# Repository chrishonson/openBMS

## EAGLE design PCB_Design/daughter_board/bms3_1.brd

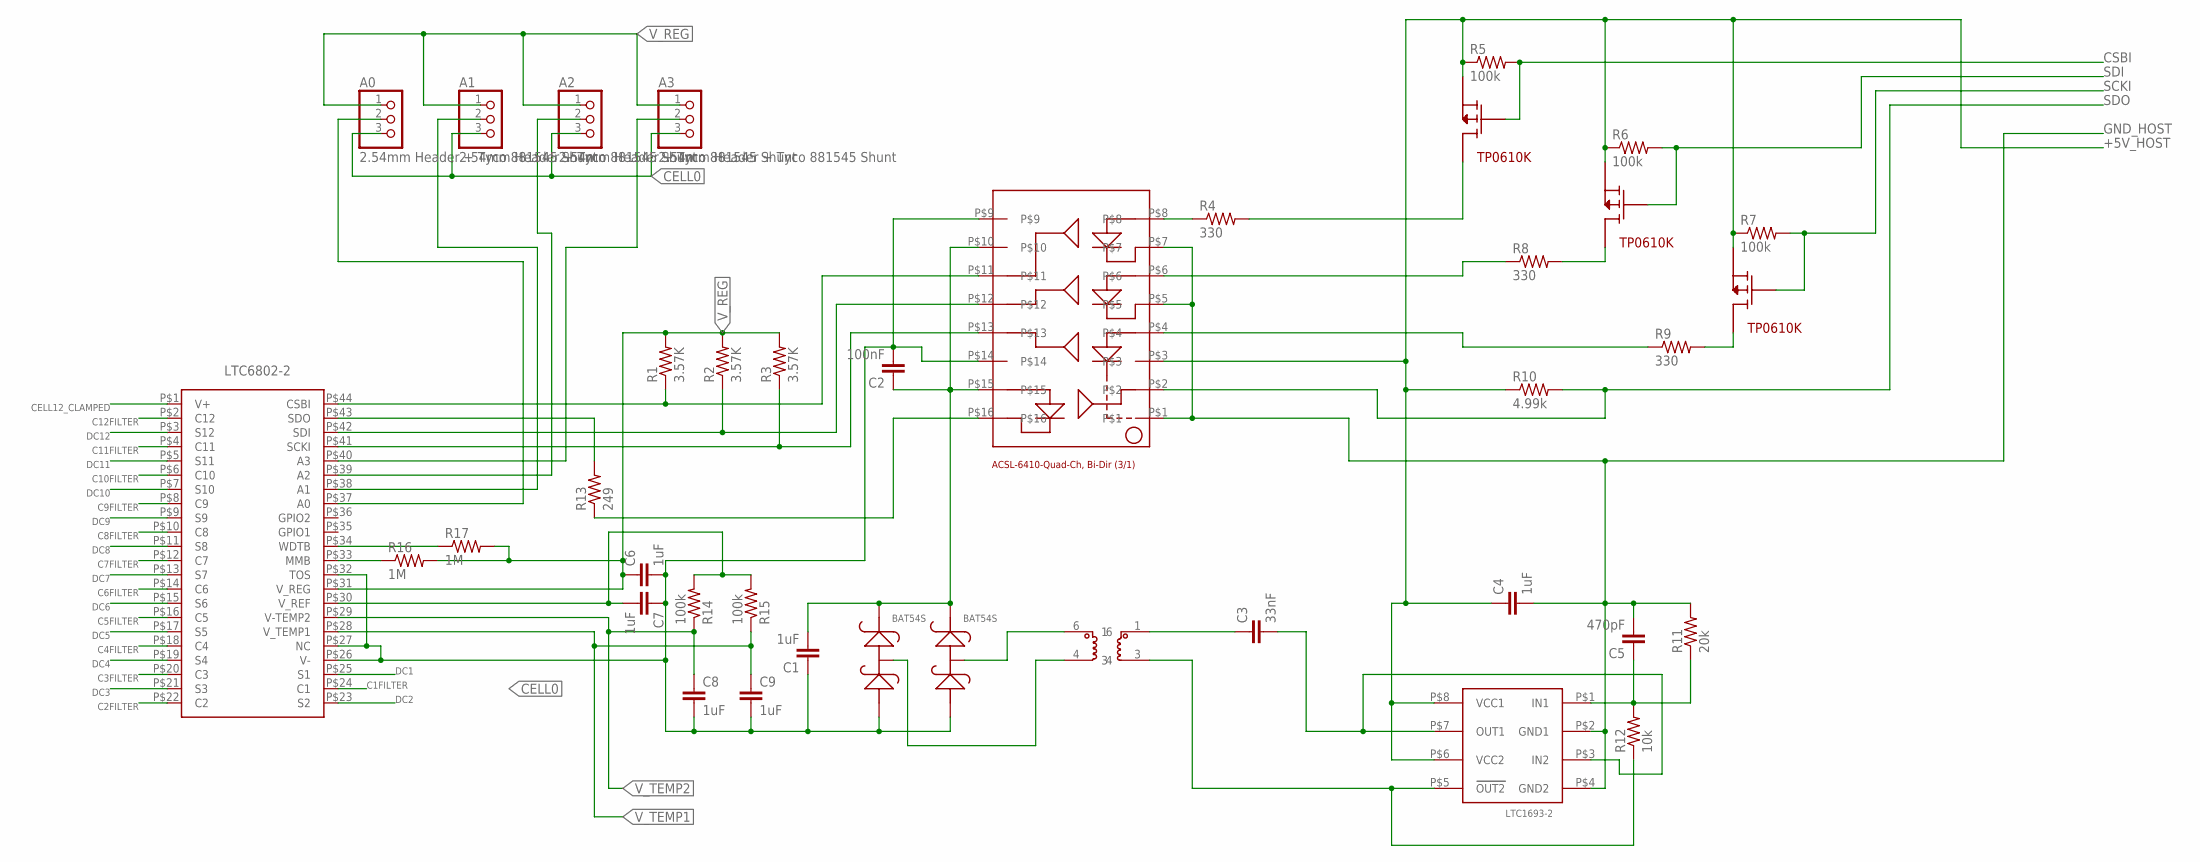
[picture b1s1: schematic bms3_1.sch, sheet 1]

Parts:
A0, A1, A2, A3: 2.54mm Header + Tyco 881545 Shunt; 1X03
ACSL6410: ACSL-6410; ACSL-6410-SO16
BAT1, BAT2: BAT54S; SOT-23
C1, C4, C6, C7, C8, C9: 1uF; C0603
C2: 100nF; C0603
C3: 33nF; C0603
C5: 470pF; C0603
CSBI: TP0610K; SOT-23
LTC1693: LTC1693-2; S8-LTC1693-2
PE68386: PE68386
R1, R2, R3: 3.57K; R0603
R4, R8, R9: 330; R0603
R5, R6, R7, R14, R15: 100k; R0603
R10: 4.99k; R0603
R11: 20k; R0603
R12: 10k; R0603
R13: 249; R0603
R16, R17: 1M; R0603
SCKI: TP0610K; SOT-23
SDI: TP0610K; SOT-23
X-BMS: LTC6802-2; SSOP-44

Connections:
+5V_HOST: ACSL6410.P$3, C4.1, CSBI.2, LTC1693.P$6 (VCC2), LTC1693.P$8 (VCC1), R5.1, R6.1, R7.1, R10.1, SCKI.2, SDI.2; also elsewhere on the board
C1FILTER: X-BMS.P$24 (C1); also elsewhere on the board
C2FILTER: X-BMS.P$22 (C2); also elsewhere on the board
C3FILTER: X-BMS.P$20 (C3); also elsewhere on the board
C4FILTER: X-BMS.P$18 (C4); also elsewhere on the board
C5FILTER: X-BMS.P$16 (C5); also elsewhere on the board
C6FILTER: X-BMS.P$14 (C6); also elsewhere on the board
C7FILTER: X-BMS.P$12 (C7); also elsewhere on the board
C8FILTER: X-BMS.P$10 (C8); also elsewhere on the board
C9FILTER: X-BMS.P$8 (C9); also elsewhere on the board
C10FILTER: X-BMS.P$6 (C10); also elsewhere on the board
C11FILTER: X-BMS.P$4 (C11); also elsewhere on the board
C12FILTER: X-BMS.P$2 (C12); also elsewhere on the board
CELL0: A0.3, A1.3, A2.3, A3.3, ACSL6410.P$9, ACSL6410.P$14, BAT1.1, BAT2.1, C1.1, C2.2, C6.2, C7.1, C8.2, C9.2, X-BMS.P$26 (V-), X-BMS.P$27 (NC), X-BMS.P$32 (TOS); also elsewhere on the board
CELL12_CLAMPED: X-BMS.P$1 (V+); also elsewhere on the board
CSBI: CSBI.1, R5.2; also elsewhere on the board
DC1: X-BMS.P$25 (S1); also elsewhere on the board
DC2: X-BMS.P$23 (S2); also elsewhere on the board
DC3: X-BMS.P$21 (S3); also elsewhere on the board
DC4: X-BMS.P$19 (S4); also elsewhere on the board
DC5: X-BMS.P$17 (S5); also elsewhere on the board
DC6: X-BMS.P$15 (S6); also elsewhere on the board
DC7: X-BMS.P$13 (S7); also elsewhere on the board
DC8: X-BMS.P$11 (S8); also elsewhere on the board
DC9: X-BMS.P$9 (S9); also elsewhere on the board
DC10: X-BMS.P$7 (S10); also elsewhere on the board
DC11: X-BMS.P$5 (S11); also elsewhere on the board
DC12: X-BMS.P$3 (S12); also elsewhere on the board
GND_HOST: ACSL6410.P$1, ACSL6410.P$5, ACSL6410.P$7, C4.2, C5.2, LTC1693.P$2 (GND1), LTC1693.P$4 (GND2), R11.2; also elsewhere on the board
unnamed: ACSL6410.P$11, R1.1, X-BMS.P$44 (CSBI)
unnamed: A3.2, X-BMS.P$40 (A3)
unnamed: ACSL6410.P$12, R2.1, X-BMS.P$42 (SDI)
unnamed: ACSL6410.P$13, R3.1, X-BMS.P$41 (SCKI)
unnamed: A2.2, X-BMS.P$39 (A2)
unnamed: A1.2, X-BMS.P$38 (A1)
unnamed: ACSL6410.P$16, R13.1
unnamed: R13.2, X-BMS.P$43 (SDO)
unnamed: BAT2.3, PE68386.6
unnamed: BAT1.3, PE68386.4
unnamed: R8.2, SDI.3
unnamed: C3.1, PE68386.1
unnamed: LTC1693.P$5 (OUT2), PE68386.3, R12.1
unnamed: C3.2, LTC1693.P$3 (IN2), LTC1693.P$7 (OUT1)
unnamed: A0.2, X-BMS.P$37 (A0)
unnamed: ACSL6410.P$6, R8.1
unnamed: C5.1, LTC1693.P$1 (IN1), R11.1, R12.2
unnamed: R9.2, SCKI.3
unnamed: ACSL6410.P$4, R9.1
unnamed: R17.1, X-BMS.P$34 (WDTB)
unnamed: R16.1, X-BMS.P$33 (MMB)
unnamed: ACSL6410.P$8, R4.1
unnamed: CSBI.3, R4.2
unnamed: ACSL6410.P$10, ACSL6410.P$15, BAT1.2, BAT2.2, C1.2, C2.1
SCKI: R7.2, SCKI.1; also elsewhere on the board
SDI: R6.2, SDI.1; also elsewhere on the board
SDO: ACSL6410.P$2, R10.2; also elsewhere on the board
V_REF: C7.2, R14.2, R15.2, X-BMS.P$30 (V_REF)
V_REG: A0.1, A1.1, A2.1, A3.1, C6.1, R1.2, R2.2, R3.2, R16.2, R17.2, X-BMS.P$31 (V_REG)
V_TEMP1: C9.1, R15.1, X-BMS.P$28 (V_TEMP1); also elsewhere on the board
V_TEMP2: C8.1, R14.1, X-BMS.P$29 (V-TEMP2); also elsewhere on the board

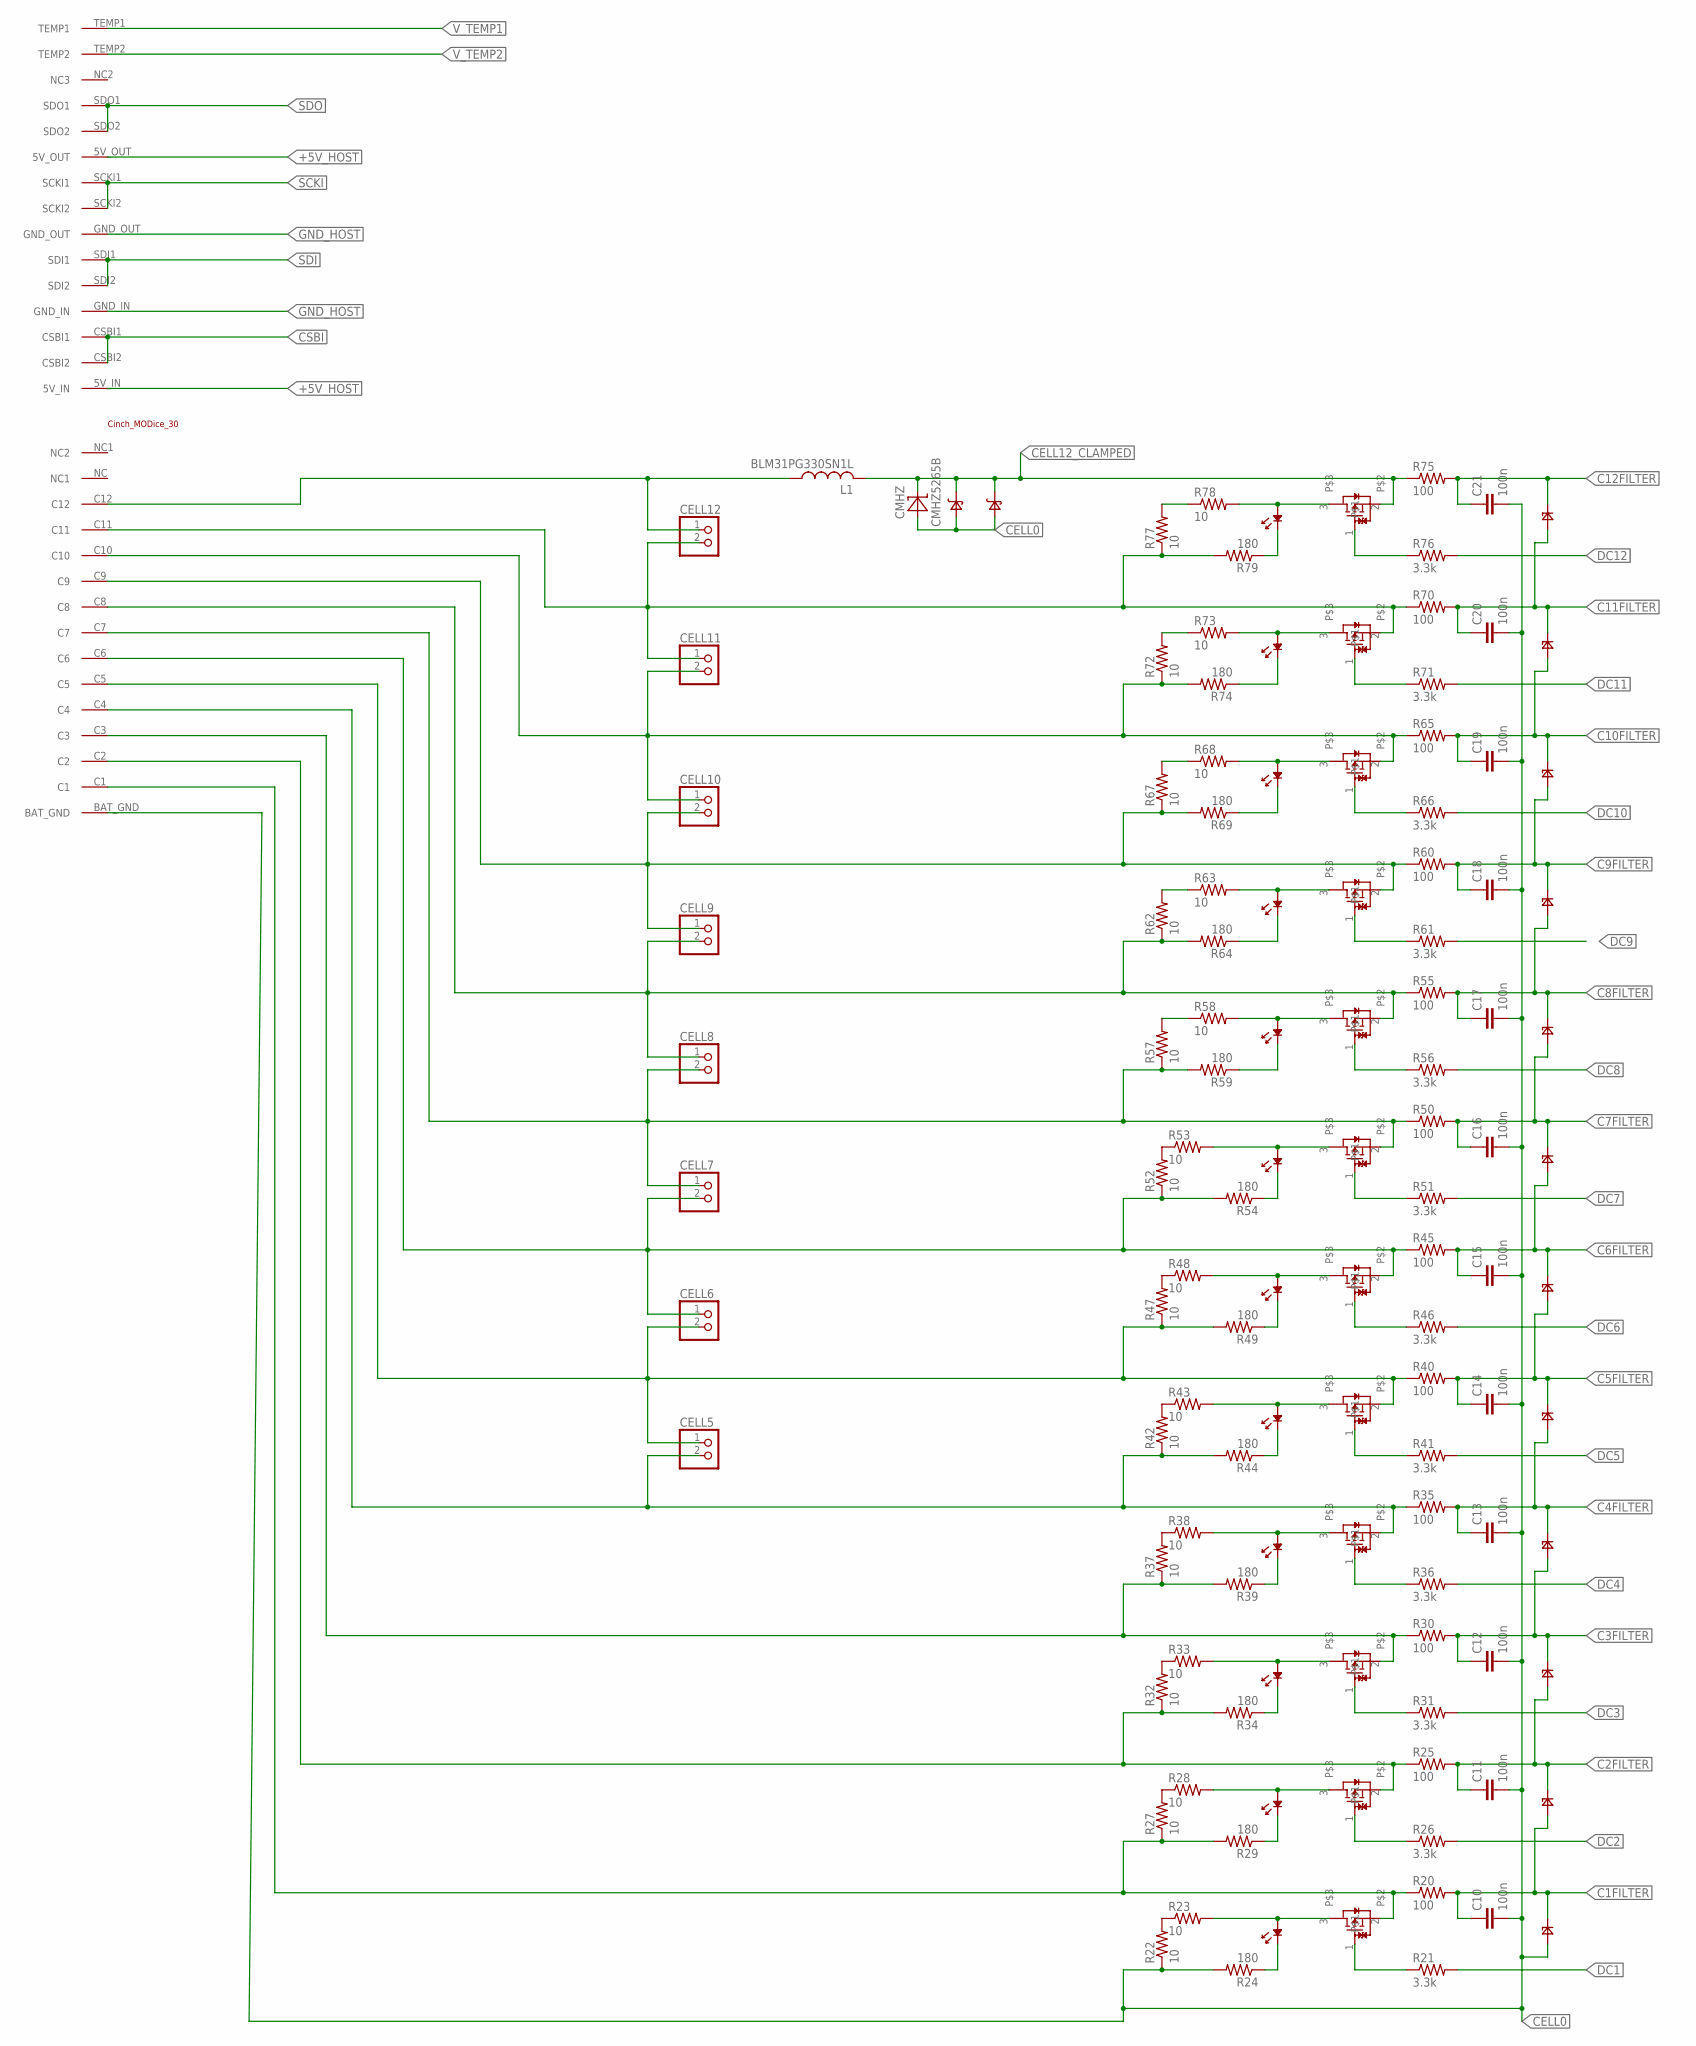
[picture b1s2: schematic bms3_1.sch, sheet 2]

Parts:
BAT3, BAT4: BAT46W; SOD123
C10, C11, C12, C13, C14, C15, C16, C17, C18, C19, C20, C21: 100n; C0603
CELL5, CELL6, CELL7, CELL8, CELL9, CELL10, CELL11, CELL12: PINHD-1X2; 1X02
CMHZ: CMHZ5265B; SOD123
L1: BLM31PG330SN1L; L3216C
LED1, LED2, LED3, LED4, LED5, LED6, LED7, LED8, LED9, LED10, LED11, LED12: LED-0805; 0805
MODICE: MODICE_30; CINCH_HEADER30
PD1, PD2, PD3, PD4, PD5, PD6, PD7, PD8, PD9, PD10, PD11, PD12: PDZ7.5B; SOD323
R20, R25, R30, R35, R40, R45, R50, R55, R60, R65, R70, R75: 100; R0603
R21, R26, R31, R36, R41, R46, R51, R56, R61, R66, R71, R76: 3.3k; R0603
R22, R23, R27, R28, R32, R33, R37, R38, R42, R43, R47, R48, R52, R53, R57, R58, R62, R63, R67, R68, R72, R73, R77, R78: 10; R2512
R24, R29, R34, R39, R44, R49, R54, R59, R64, R69, R74, R79: 180; R0805
T1, T2, T3, T4, T5, T6, T7, T8, T9, T10, T11, T12: RTR020P02; TSMT3

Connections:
+5V_HOST: MODICE.5V_IN, MODICE.5V_OUT; also elsewhere on the board
C1FILTER: C10.1, PD1.P$1, PD2.P$2, R20.2; also elsewhere on the board
C2FILTER: C11.1, PD2.P$1, PD3.P$2, R25.2; also elsewhere on the board
C3FILTER: C12.1, PD3.P$1, PD4.P$2, R30.2; also elsewhere on the board
C4FILTER: C13.1, PD4.P$1, PD5.P$2, R35.2; also elsewhere on the board
C5FILTER: C14.1, PD5.P$1, PD6.P$2, R40.2; also elsewhere on the board
C6FILTER: C15.1, PD6.P$1, PD7.P$2, R45.2; also elsewhere on the board
C7FILTER: C16.1, PD7.P$1, PD8.P$2, R50.2; also elsewhere on the board
C8FILTER: C17.1, PD8.P$1, PD9.P$2, R55.2; also elsewhere on the board
C9FILTER: C18.1, PD9.P$1, PD10.P$2, R60.2; also elsewhere on the board
C10FILTER: C19.1, PD10.P$1, PD11.P$2, R65.2; also elsewhere on the board
C11FILTER: C20.1, PD11.P$1, PD12.P$2, R70.2; also elsewhere on the board
C12FILTER: C21.1, PD12.P$1, R75.2; also elsewhere on the board
CELL0: BAT3.POS, BAT4.POS, C10.2, C11.2, C12.2, C13.2, C14.2, C15.2, C16.2, C17.2, C18.2, C19.2, C20.2, C21.2, CMHZ.POS (A), MODICE.BAT_GND, PD1.P$2, R22.1, R24.2; also elsewhere on the board
CELL1: MODICE.C1, R20.1, R27.1, R29.2, T1.2
CELL2: MODICE.C2, R25.1, R32.1, R34.2, T2.2
CELL3: MODICE.C3, R30.1, R37.1, R39.2, T3.2
CELL4: CELL5.2, MODICE.C4, R35.1, R42.1, R44.2, T4.2
CELL5: CELL5.1, CELL6.2, MODICE.C5, R40.1, R47.1, R49.2, T5.2
CELL6: CELL6.1, CELL7.2, MODICE.C6, R45.1, R52.1, R54.2, T6.2
CELL7: CELL7.1, CELL8.2, MODICE.C7, R50.1, R57.1, R59.2, T7.2
CELL8: CELL8.1, CELL9.2, MODICE.C8, R55.1, R62.1, R64.2, T8.2
CELL9: CELL9.1, CELL10.2, MODICE.C9, R60.1, R67.1, R69.2, T9.2
CELL10: CELL10.1, CELL11.2, MODICE.C10, R65.1, R72.1, R74.2, T10.2
CELL11: CELL11.1, CELL12.2, MODICE.C11, R70.1, R77.1, R79.2, T11.2
CELL12: CELL12.1, L1.1, MODICE.C12
CELL12_CLAMPED: BAT3.NEG, BAT4.NEG, CMHZ.NEG (C), L1.2, R75.1, T12.2; also elsewhere on the board
CSBI: MODICE.CSBI1, MODICE.CSBI2; also elsewhere on the board
DC1: R21.2; also elsewhere on the board
DC2: R26.2; also elsewhere on the board
DC3: R31.2; also elsewhere on the board
DC4: R36.2; also elsewhere on the board
DC5: R41.2; also elsewhere on the board
DC6: R46.2; also elsewhere on the board
DC7: R51.2; also elsewhere on the board
DC8: R56.2; also elsewhere on the board
DC9: R61.2; also elsewhere on the board
DC10: R66.2; also elsewhere on the board
DC11: R71.2; also elsewhere on the board
DC12: R76.2; also elsewhere on the board
GND_HOST: MODICE.GND_IN, MODICE.GND_OUT; also elsewhere on the board
LED3: LED3.P$1, R34.1
unnamed: R77.2, R78.1
unnamed: LED1.P$2, R23.2, T1.3
unnamed: LED1.P$1, R24.1
unnamed: LED2.P$2, R28.2, T2.3
unnamed: R21.1, T1.1
unnamed: R72.2, R73.1
unnamed: R67.2, R68.1
unnamed: LED2.P$1, R29.1
unnamed: R26.1, T2.1
unnamed: R62.2, R63.1
unnamed: LED9.P$2, R63.2, T9.3
unnamed: R57.2, R58.1
unnamed: LED3.P$2, R33.2, T3.3
unnamed: R52.2, R53.1
unnamed: R31.1, T3.1
unnamed: R47.2, R48.1
unnamed: LED4.P$2, R38.2, T4.3
unnamed: LED4.P$1, R39.1
unnamed: R42.2, R43.1
unnamed: R37.2, R38.1
unnamed: LED9.P$1, R64.1
unnamed: R32.2, R33.1
unnamed: LED5.P$2, R43.2, T5.3
unnamed: LED5.P$1, R44.1
unnamed: R41.1, T5.1
unnamed: R27.2, R28.1
unnamed: LED6.P$2, R48.2, T6.3
unnamed: LED6.P$1, R49.1
unnamed: R46.1, T6.1
unnamed: R22.2, R23.1
unnamed: R61.1, T9.1
unnamed: LED7.P$2, R53.2, T7.3
unnamed: LED7.P$1, R54.1
unnamed: R51.1, T7.1
unnamed: LED8.P$2, R58.2, T8.3
unnamed: LED8.P$1, R59.1
unnamed: R56.1, T8.1
unnamed: LED10.P$2, R68.2, T10.3
unnamed: LED10.P$1, R69.1
unnamed: R66.1, T10.1
unnamed: LED11.P$2, R73.2, T11.3
unnamed: LED11.P$1, R74.1
unnamed: R71.1, T11.1
unnamed: LED12.P$2, R78.2, T12.3
unnamed: LED12.P$1, R79.1
unnamed: R76.1, T12.1
SCKI: MODICE.SCKI1, MODICE.SCKI2; also elsewhere on the board
SDI: MODICE.SDI1, MODICE.SDI2; also elsewhere on the board
SDO: MODICE.SDO1, MODICE.SDO2; also elsewhere on the board
T4: R36.1, T4.1
V_TEMP1: MODICE.TEMP1; also elsewhere on the board
V_TEMP2: MODICE.TEMP2; also elsewhere on the board

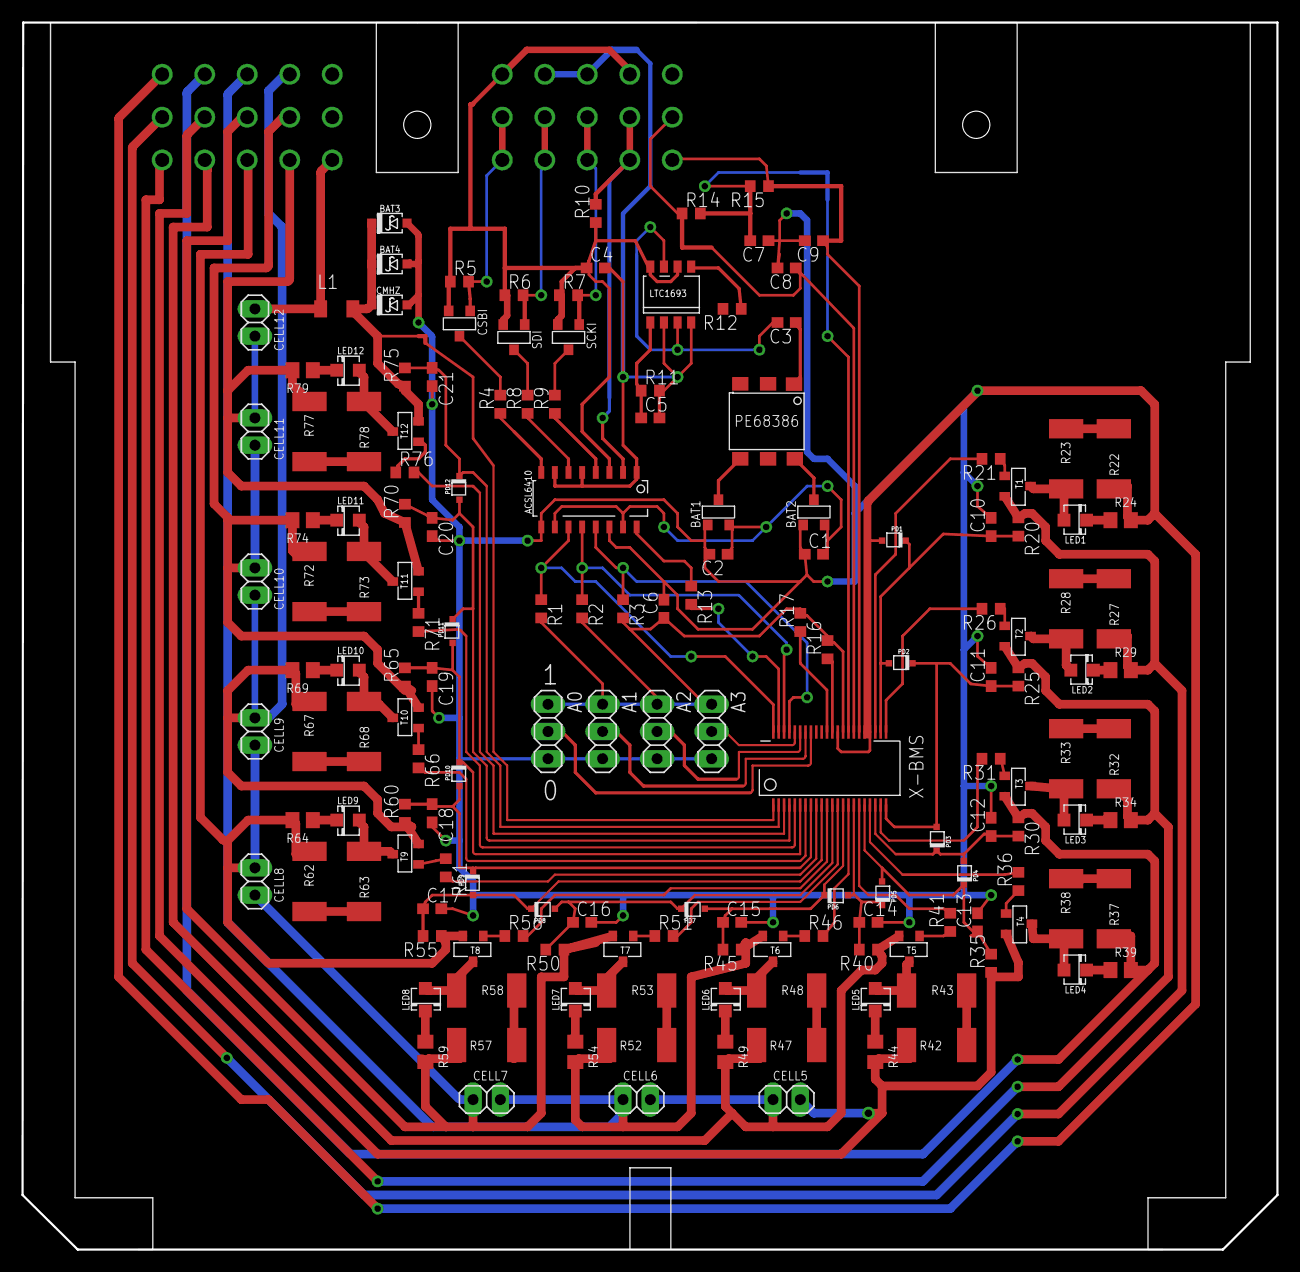
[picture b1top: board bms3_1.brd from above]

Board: 2 copper layers, 116.9 x 114.3 mm, 160 parts (0 on the bottom side), 120 nets.

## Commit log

2012-02-22 Master Shield first commits
2012-02-22 Proposal for connection with CAN-bus
2012-02-24 * Removed spaces from directory names so that Eagle can find them directly
    New schema for OpenBMS Master card:
    + 3 x optically isolated SSR's (max 60V / 4A each)
2012-02-24 + Git ignore
2012-02-24 - .DS_Store-files
2012-03-04 Preparing for BatchPCB test-run
2012-10-20 replacing 0402 with 0603
2012-10-20 more 0603
